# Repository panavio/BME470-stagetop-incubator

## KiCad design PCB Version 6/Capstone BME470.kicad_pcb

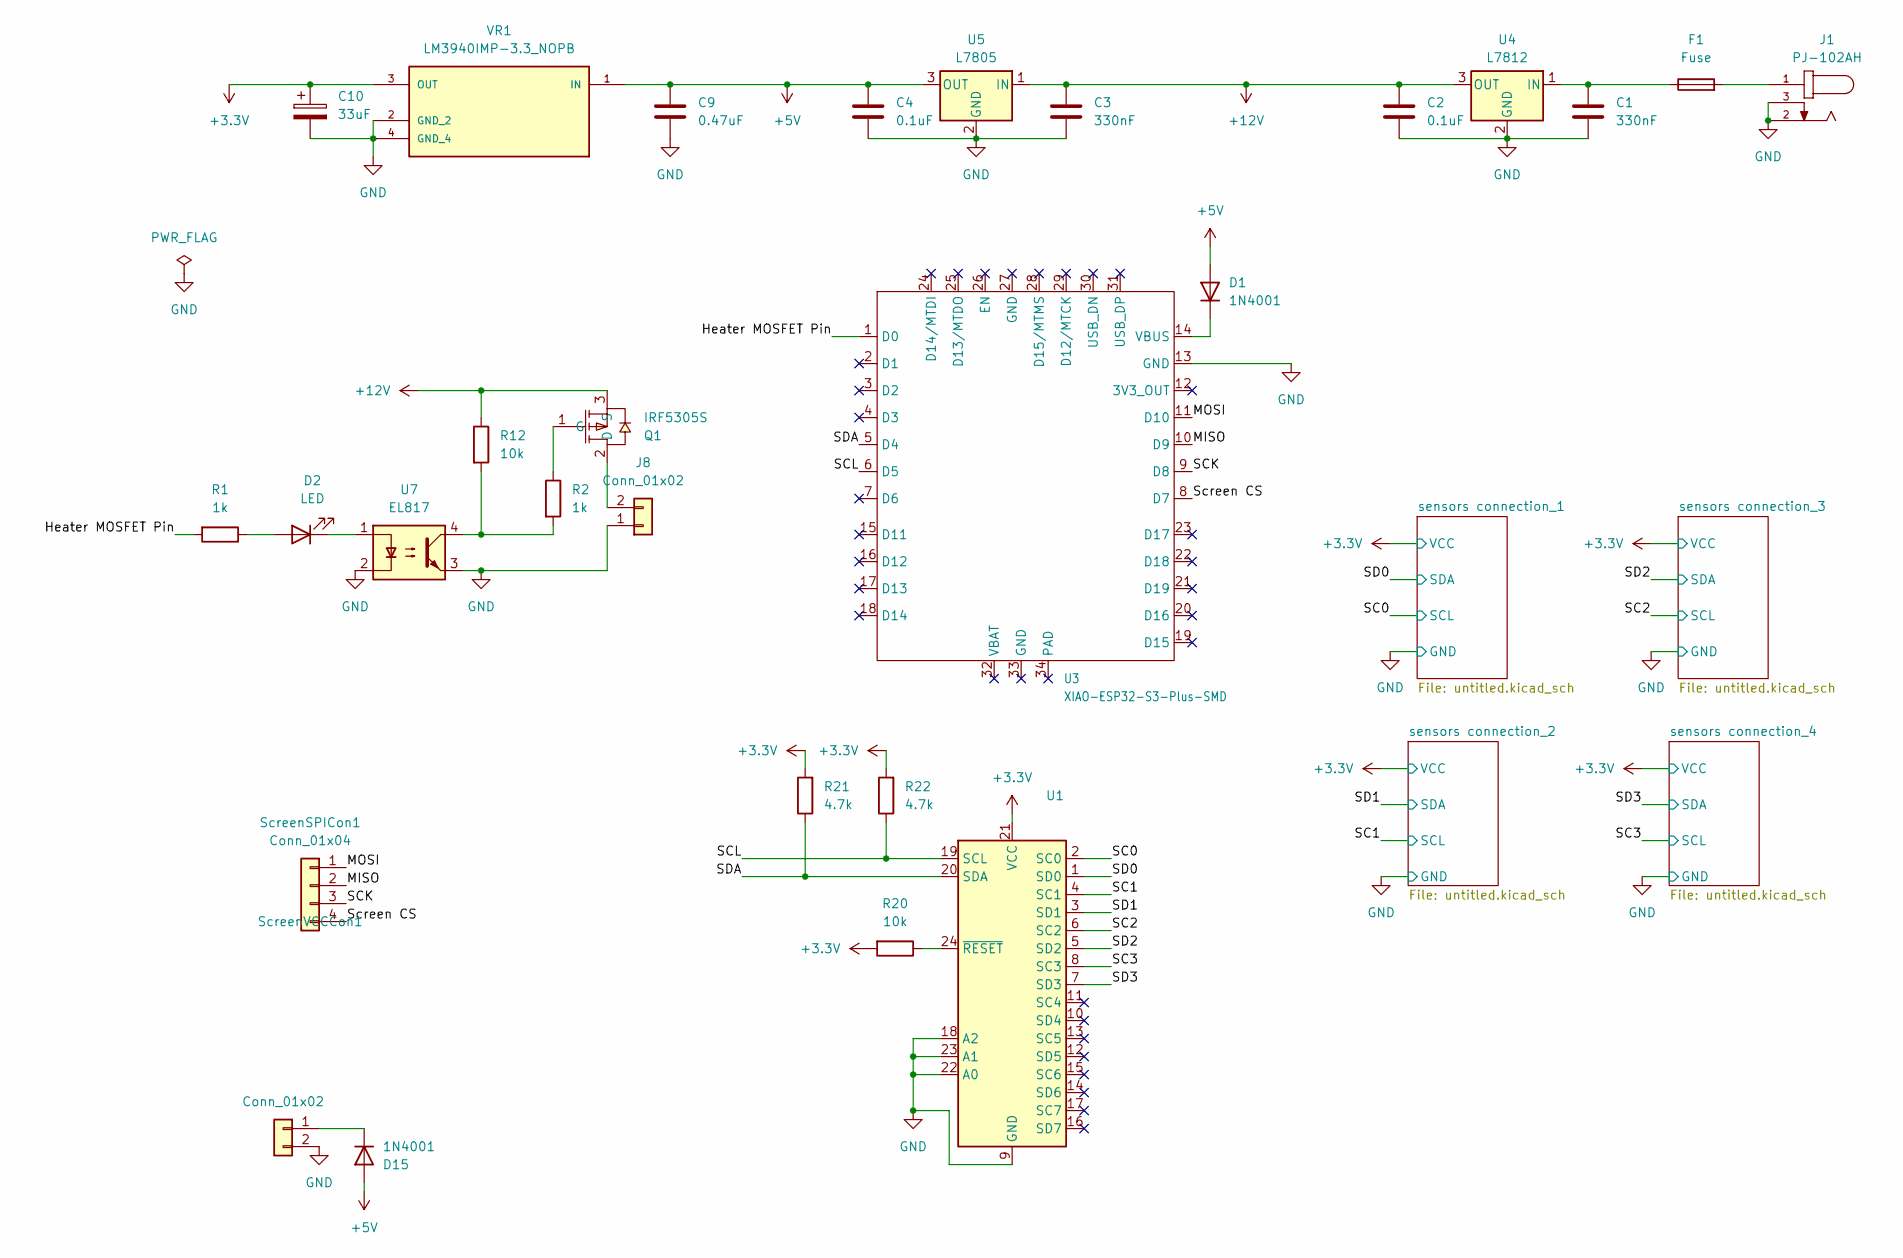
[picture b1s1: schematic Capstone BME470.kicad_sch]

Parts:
C1, C3: 330nF; C_0805_2012Metric; LCSC Part # C2228302
C2, C4: 0.1uF; C_0805_2012Metric; LCSC Part # C49678
C9: 0.47uF; C_0805_2012Metric; LCSC Part # C437481
C10: 33uF; CP_EIA-6032-28_Kemet-C_HandSolder; LCSC Part # C1958890
D1, D15: 1N4001; D_DO-41_SOD81_P10.16mm_Horizontal; LCSC Part # C2456
D2: LED; LED_0805_2012Metric; LCSC Part # C2295
F1: Fuse; R_Axial_DIN0207_L6.3mm_D2.5mm_P7.62mm_Horizontal; LCSC Part # DNP
J1: PJ-102AH; BarrelJack_CUI_PJ-102AH_Horizontal; MPN PJ-102AH; LCSC Part # C3096093
J8: Conn_01x02; PinHeader_1x02_P2.54mm_Vertical; LCSC Part # DNP
Q1: IRF5305S; TO-263-2; MPN IRF5305PBF; LCSC Part C41224
R1, R2: 1k; R_0805_2012Metric; LCSC Part # C17513
R12, R20: 10k; R_0805_2012Metric; LCSC Part # C17414
R21, R22: 4.7k; R_0805_2012Metric; LCSC Part # C17673
ScreenSPICon1: Conn_01x04; JST_GH_BM04B-GHS-TBT_1x04-1MP_P1.25mm_Vertical; LCSC Part # C20089142
ScreenVCCCon1: Conn_01x02; PinHeader_1x02_P2.54mm_Vertical; LCSC Part # DNP
U1: TCA9548AMRGER; Texas_RGE0024C_VQFN-24-1EP_4x4mm_P0.5mm_EP2.1x2.1mm; LCSC Part # C2876717
U3: XIAO-ESP32-S3-Plus-SMD; LCSC Part # C9900290869
U4: L7812; TO-252-2; LCSC Part # C55337847
U5: L7805; TO-252-2; LCSC Part # C310413
U7: EL817; DIP-4_W7.62mm; LCSC Part # C5353
VR1: LM3940IMP-3.3_NOPB; SOT-223; MPN LM3940IMP-3.3/NOPB; LCSC Part # C140319

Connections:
+3.3V: C10.1, R20.2, R21.2, R22.2, U1.21 (VCC), VR1.3 (OUT); also elsewhere on the board
+5V: C4.1, C9.1, D1.2 (A), D15.2 (A), U5.3 (OUT), VR1.1 (IN)
+12V: C2.1, C3.1, Q1.3 (S), R12.1, U4.3 (OUT), U5.1 (IN)
/Heater MOSFET Pin: R1.2, U3.1 (D0)
/MISO: ScreenSPICon1.2, U3.10 (D9)
/MOSI: ScreenSPICon1.1, U3.11 (D10)
/SC0: U1.2 (SC0); also elsewhere on the board
/SC1: U1.4 (SC1); also elsewhere on the board
/SC2: U1.6 (SC2); also elsewhere on the board
/SC3: U1.8 (SC3); also elsewhere on the board
/SCK: ScreenSPICon1.3, U3.9 (D8)
/SCL: R22.1, U1.19 (SCL), U3.6 (D5)
/SD0: U1.1 (SD0); also elsewhere on the board
/SD1: U1.3 (SD1); also elsewhere on the board
/SD2: U1.5 (SD2); also elsewhere on the board
/SD3: U1.7 (SD3); also elsewhere on the board
/SDA: R21.1, U1.20 (SDA), U3.5 (D4)
/Screen CS: ScreenSPICon1.4, U3.8 (D7)
GND: C1.2, C2.2, C3.2, C4.2, C9.2, C10.2, J1.2, J1.3, J8.1, ScreenVCCCon1.2, U1.9 (GND), U1.18 (A2), U1.22 (A0), U1.23 (A1), U3.13 (GND), U4.2 (GND), U5.2 (GND), U7.2, U7.3, VR1.2 (GND_2), VR1.4 (GND_4); also elsewhere on the board
unnamed: D1.1 (K), U3.14 (VBUS)
unnamed: D2.2 (A), R1.1
unnamed: D2.1 (K), U7.1
unnamed: D15.1 (K), ScreenVCCCon1.1
unnamed: F1.2, J1.1
unnamed: J8.2, Q1.2 (D)
unnamed: Q1.1 (G), R2.1
unnamed: R2.2, R12.2, U7.4
unnamed: R20.1, U1.24 (~RESET)
unnamed: C1.1, F1.1, U4.1 (IN)

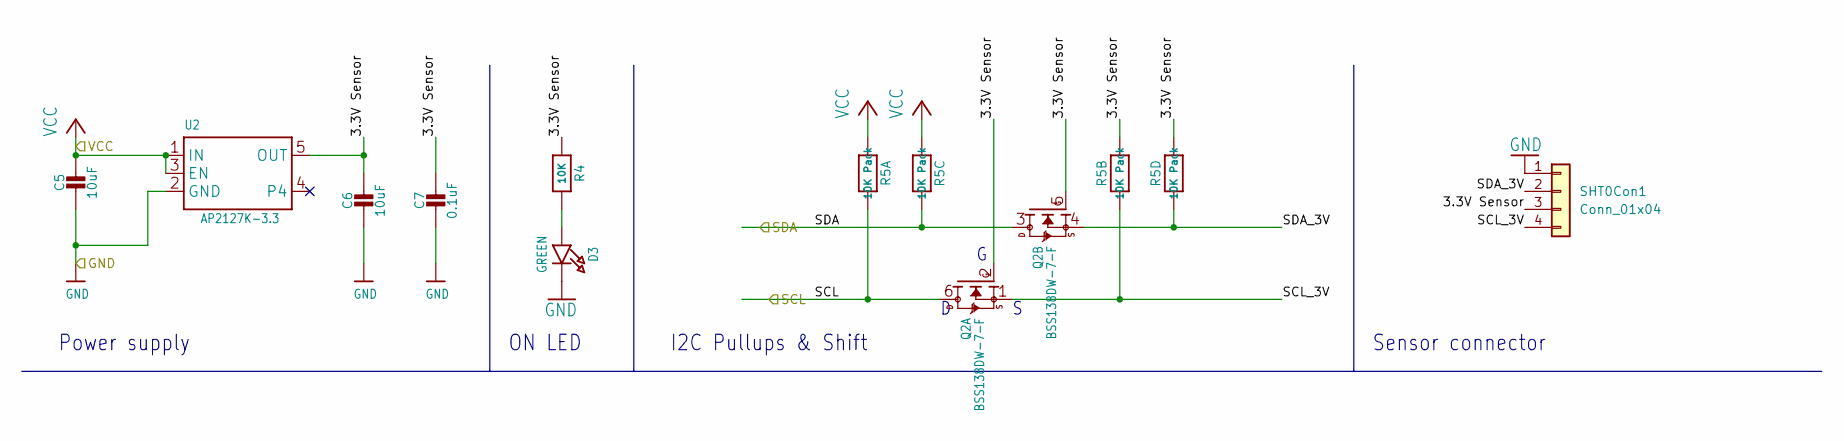
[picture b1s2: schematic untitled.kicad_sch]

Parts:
C5: 10uF; C_0805_2012Metric_Pad1.18x1.45mm_HandSolder; LCSC Part # C15850
C6: 10uF; C_0805_2012Metric; LCSC Part # C15850
C7: 0.1uF; 0603-NO; LCSC Part # C14663
D3: GREEN; CHIPLED_0603_NOOUTLINE; LCSC Part # C72043
Q2: BSS138DW-7-F; SOT363; LCSC Part # C154900
R4: 10K; 0603-NO; LCSC Part # C25804
R5: 10K Pack; RESPACK_4X0603; LCSC Part # C29718
SHT0Con1: Conn_01x04; JST_GH_BM04B-GHS-TBT_1x04-1MP_P1.25mm_Vertical; LCSC Part # C20089142
U2: AP2127K-3.3; SOT23-5; LCSC Part # C156285

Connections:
+3.3V: C5.1, R5.1, R5.3 (1), U2.1 (IN), U2.3 (EN); also elsewhere on the board
/SC0: Q2.6 (D), R5.8 (2); also elsewhere on the board
/SD0: Q2.3 (D), R5.6 (2); also elsewhere on the board
/sensors connection_1/3.3V Sensor: C6.1, C7.1, Q2.2 (G), Q2.5 (G), R4.1, R5.2 (1), R5.4 (1), SHT0Con1.3, U2.5 (OUT)
/sensors connection_1/SCL_3V: Q2.1 (S), R5.7 (2), SHT0Con1.4
/sensors connection_1/SDA_3V: Q2.4 (S), R5.5 (2), SHT0Con1.2
GND: C5.2, C6.2, C7.2, D3.C, SHT0Con1.1, U2.2 (GND); also elsewhere on the board
unnamed: D3.A, R4.2

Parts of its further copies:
C8, C11, C16: 10uF; C_0805_2012Metric_Pad1.18x1.45mm_HandSolder; LCSC Part # C15850
C12, C14, C17: 10uF; C_0805_2012Metric; LCSC Part # C15850
C13, C15, C18: 0.1uF; 0603-NO; LCSC Part # C14663
D5, D6, D7: GREEN; CHIPLED_0603_NOOUTLINE; LCSC Part # C72043
Q3, Q4, Q5: BSS138DW-7-F; SOT363; LCSC Part # C154900
R6, R8, R10: 10K; 0603-NO; LCSC Part # C25804
R7, R9, R11: 10K Pack; RESPACK_4X0603; LCSC Part # C29718
SHT1Con1, SHT2Con1, SHT3Con1: Conn_01x04; JST_GH_BM04B-GHS-TBT_1x04-1MP_P1.25mm_Vertical; LCSC Part # C20089142
U6, U9, U10: AP2127K-3.3; SOT23-5; LCSC Part # C156285

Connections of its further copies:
+3.3V: C8.1, C11.1, C16.1, R7.1, R7.3 (1), R9.1, R9.3 (1), R11.1, R11.3 (1), U6.1 (IN), U6.3 (EN), U9.1 (IN), U9.3 (EN), U10.1 (IN), U10.3 (EN); also elsewhere on the board
/SC1: Q3.6 (D), R7.8 (2); also elsewhere on the board
/SC2: Q4.6 (D), R9.8 (2); also elsewhere on the board
/SC3: Q5.6 (D), R11.8 (2); also elsewhere on the board
/SD1: Q3.3 (D), R7.6 (2); also elsewhere on the board
/SD2: Q4.3 (D), R9.6 (2); also elsewhere on the board
/SD3: Q5.3 (D), R11.6 (2); also elsewhere on the board
/sensors connection_2/3.3V Sensor: C12.1, C13.1, Q3.2 (G), Q3.5 (G), R6.1, R7.2 (1), R7.4 (1), SHT1Con1.3, U6.5 (OUT)
/sensors connection_2/SCL_3V: Q3.1 (S), R7.7 (2), SHT1Con1.4
/sensors connection_2/SDA_3V: Q3.4 (S), R7.5 (2), SHT1Con1.2
/sensors connection_3/3.3V Sensor: C14.1, C15.1, Q4.2 (G), Q4.5 (G), R8.1, R9.2 (1), R9.4 (1), SHT2Con1.3, U9.5 (OUT)
/sensors connection_3/SCL_3V: Q4.1 (S), R9.7 (2), SHT2Con1.4
/sensors connection_3/SDA_3V: Q4.4 (S), R9.5 (2), SHT2Con1.2
/sensors connection_4/3.3V Sensor: C17.1, C18.1, Q5.2 (G), Q5.5 (G), R10.1, R11.2 (1), R11.4 (1), SHT3Con1.3, U10.5 (OUT)
/sensors connection_4/SCL_3V: Q5.1 (S), R11.7 (2), SHT3Con1.4
/sensors connection_4/SDA_3V: Q5.4 (S), R11.5 (2), SHT3Con1.2
GND: C8.2, C11.2, C12.2, C13.2, C14.2, C15.2, C16.2, C17.2, C18.2, D5.C, D6.C, D7.C, SHT1Con1.1, SHT2Con1.1, SHT3Con1.1, U6.2 (GND), U9.2 (GND), U10.2 (GND); also elsewhere on the board
unnamed: D5.A, R6.2
unnamed: D6.A, R8.2
unnamed: D7.A, R10.2

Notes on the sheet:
ON LED
I2C Pullups & Shift
Sensor connector
Power supply

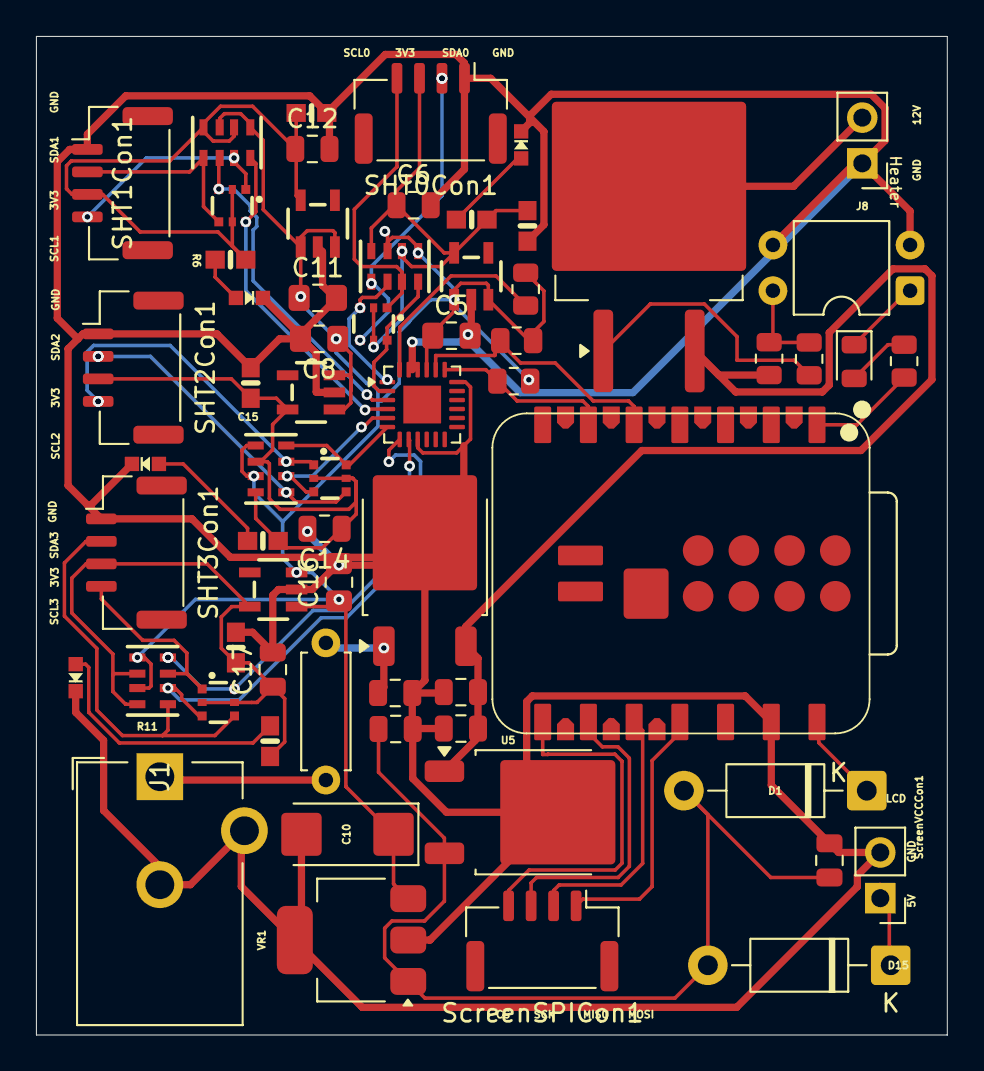
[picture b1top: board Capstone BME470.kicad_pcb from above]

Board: 2 copper layers, 50.6 x 55.5 mm, 63 parts (0 on the bottom side), 45 nets.

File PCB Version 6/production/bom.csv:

Designator,Footprint,Quantity,Value,LCSC Part #
"C1, C3",0805,2,330nF,C2228302
C10,CP_EIA-6032-28_Kemet-C_HandSolder,1,33uF,C1958890
"C11, C12, C14, C16, C17, C5, C6, C8",0805,8,10uF,C15850
"C13, C15, C18, C7",0603-NO,4,0.1uF,C14663
"C2, C4",0805,2,0.1uF,C49678
C9,0805,1,0.47uF,C437481
"D1, D15",D_DO-41_SOD81_P10.16mm_Horizontal,2,1N4001,C2456
D2,0805,1,LED,C2295
"D3, D5, D6, D7",CHIPLED_0603_NOOUTLINE,4,GREEN,C72043
F1,R_Axial_DIN0207_L6.3mm_D2.5mm_P7.62mm_Horizontal,1,Fuse,DNP
J1,BarrelJack_CUI_PJ-102AH_Horizontal,1,PJ-102AH,C3096093 
"J8, SCREENVCCCON1",PinHeader_1x02_P2.54mm_Vertical,2,Conn_01x02,DNP
Q1,TO-263-2,1,IRF5305S,C41224
"Q2, Q3, Q4, Q5",SOT363,4,BSS138DW-7-F,C154900
"R1, R2",0805,2,1k,C17513
"R10, R4, R6, R8",0603-NO,4,10K,C25804
"R11, R5, R7, R9",RESPACK_4X0603,4,10K Pack,C29718
"R12, R20",0805,2,10k,C17414
"R21, R22",0805,2,4.7k,C17673
"SCREENSPICON1, SHT0CON1, SHT1CON1, SHT2CON1, SHT3CON1",JST_GH_BM04B-GHS-TBT_1x04-1MP_P1.25mm_Vertical,5,Conn_01x04,C20089142
U1,Texas_RGE0024C_VQFN-24-1EP_4x4mm_P0.5mm_EP2.1x2.1mm,1,TCA9548AMRGER,C2876717
"U10, U2, U6, U9",SOT23-5,4,AP2127K-3.3,C156285
U3,XIAO-ESP32-S3-Plus-SMD,1,XIAO-ESP32-S3-Plus-SMD,C9900290869
U4,TO-252-2,1,L7812,C55337847
U5,TO-252-2,1,L7805,C310413
U7,DIP-4_W7.62mm,1,EL817,C17588427
VR1,SOT-223,1,LM3940IMP-3.3_NOPB,C140319

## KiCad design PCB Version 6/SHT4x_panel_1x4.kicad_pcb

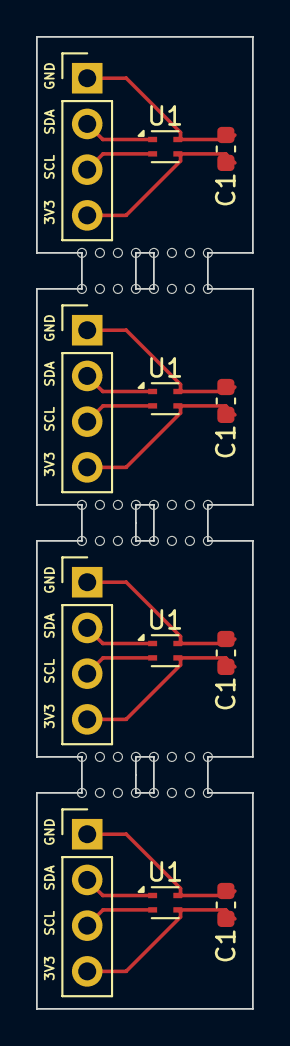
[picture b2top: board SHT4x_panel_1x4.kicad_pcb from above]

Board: 2 copper layers, 12.0 x 54.0 mm, 60 parts (0 on the bottom side), 16 nets.

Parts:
C1, C1#2, C1#3, C1#4: 100nF; C_0603_1608Metric
J1, J1#2, J1#3, J1#4: Conn_01x04; PinHeader_1x04_P2.54mm_Vertical
KiKit_MB_1_1, KiKit_MB_1_2, KiKit_MB_1_3, KiKit_MB_1_4, KiKit_MB_2_1, KiKit_MB_2_2, KiKit_MB_2_3, KiKit_MB_2_4, KiKit_MB_3_1, KiKit_MB_3_2, KiKit_MB_3_3, KiKit_MB_3_4, KiKit_MB_4_1, KiKit_MB_4_2, KiKit_MB_4_3, KiKit_MB_4_4, KiKit_MB_5_1, KiKit_MB_5_2, KiKit_MB_5_3, KiKit_MB_5_4, KiKit_MB_6_1, KiKit_MB_6_2, KiKit_MB_6_3, KiKit_MB_6_4, KiKit_MB_7_1, KiKit_MB_7_2, KiKit_MB_7_3, KiKit_MB_7_4, KiKit_MB_8_1, KiKit_MB_8_2, KiKit_MB_8_3, KiKit_MB_8_4, KiKit_MB_9_1, KiKit_MB_9_2, KiKit_MB_9_3, KiKit_MB_9_4, KiKit_MB_10_1, KiKit_MB_10_2, KiKit_MB_10_3, KiKit_MB_10_4, KiKit_MB_11_1, KiKit_MB_11_2, KiKit_MB_11_3, KiKit_MB_11_4, KiKit_MB_12_1, KiKit_MB_12_2, KiKit_MB_12_3, KiKit_MB_12_4: NPTH
U1, U1#2, U1#3, U1#4: SHT4x; Sensirion_DFN-4_1.5x1.5mm_P0.8mm_SHT4x_NoCentralPad

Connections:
Board_0-/3.3V: C1.2, J1#3.4, U1#4.3 (VDD)
Board_0-/GND: C1.1, J1#3.1, U1#4.4 (VSS)
Board_0-Net-(J1-Pin_2): J1#3.2, U1#4.1 (SDA)
Board_0-Net-(J1-Pin_3): J1#3.3, U1#4.2 (SCL)
Board_1-/3.3V: C1#3.2, J1.4, U1#3.3 (VDD)
Board_1-/GND: C1#3.1, J1.1, U1#3.4 (VSS)
Board_1-Net-(J1-Pin_2): J1.2, U1#3.1 (SDA)
Board_1-Net-(J1-Pin_3): J1.3, U1#3.2 (SCL)
Board_2-/3.3V: C1#2.2, J1#2.4, U1.3 (VDD)
Board_2-/GND: C1#2.1, J1#2.1, U1.4 (VSS)
Board_2-Net-(J1-Pin_2): J1#2.2, U1.1 (SDA)
Board_2-Net-(J1-Pin_3): J1#2.3, U1.2 (SCL)
Board_3-/3.3V: C1#4.2, J1#4.4, U1#2.3 (VDD)
Board_3-/GND: C1#4.1, J1#4.1, U1#2.4 (VSS)
Board_3-Net-(J1-Pin_2): J1#4.2, U1#2.1 (SDA)
Board_3-Net-(J1-Pin_3): J1#4.3, U1#2.2 (SCL)
